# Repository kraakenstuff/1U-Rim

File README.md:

# 1U-RIM
Eurorack 1U rimshot module based on Hexinverter's NeinOhNein Rim (https://static1.squarespace.com/static/54c8f37ae4b015761b133d43/t/550ba520e4b0c15a9e33dd91/1426826530104/?format=1000w)

Status: it worked, but I've redesigned Accent handling. This new PCB is still not tested.

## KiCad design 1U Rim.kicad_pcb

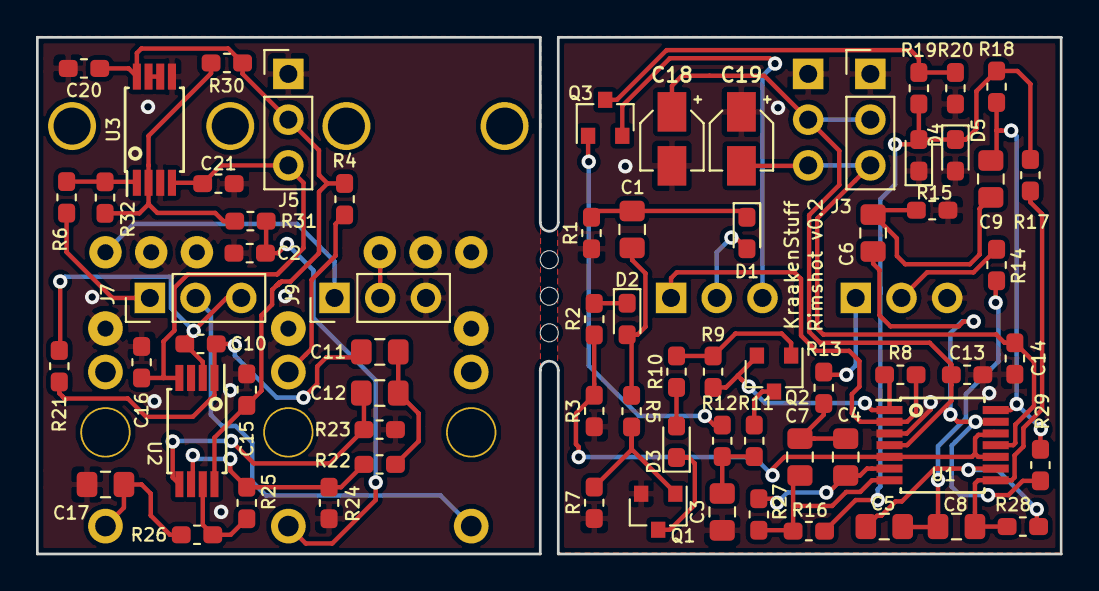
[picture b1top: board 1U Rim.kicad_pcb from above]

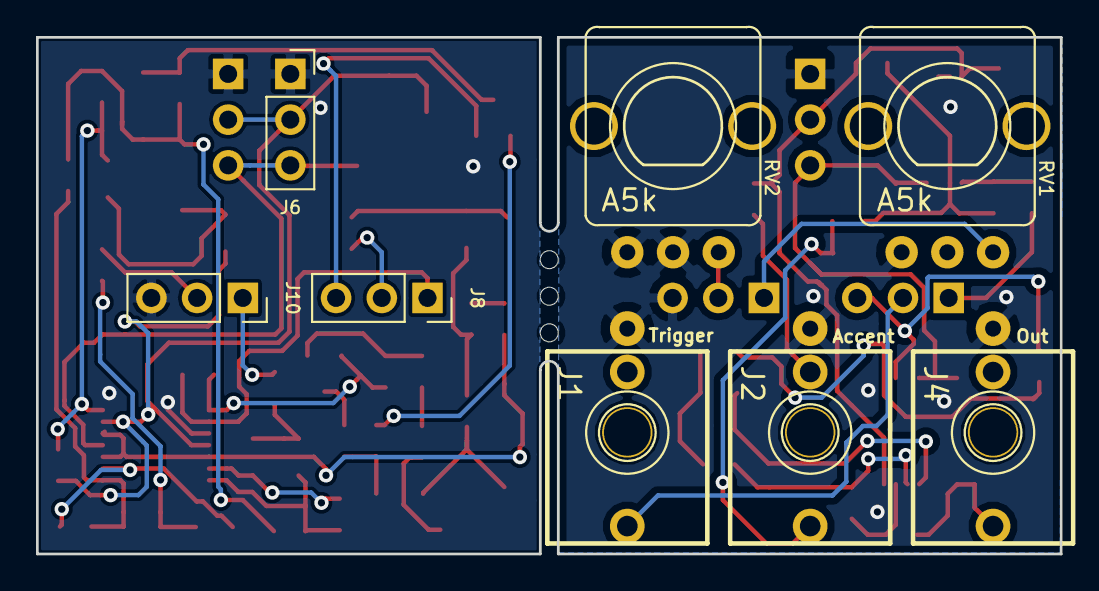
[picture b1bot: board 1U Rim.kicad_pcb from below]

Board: 2 copper layers, 56.9 x 28.7 mm, 76 parts (8 on the bottom side), 42 nets.

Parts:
C1: 18n; C_0805_2012Metric_Pad1.15x1.40mm_HandSolder
C2: 100p; C_0603_1608Metric_Pad1.05x0.95mm_HandSolder
C3: 47n; C_0805_2012Metric_Pad1.15x1.40mm_HandSolder
C4, C7, C11, C12, C17: 10n; C_0805_2012Metric_Pad1.15x1.40mm_HandSolder
C5, C8: 27n; C_0805_2012Metric_Pad1.15x1.40mm_HandSolder
C6, C9: 4.7n; C_0805_2012Metric_Pad1.15x1.40mm_HandSolder
C10: 220p; C_0603_1608Metric_Pad1.05x0.95mm_HandSolder
C13, C14, C15, C16, C20, C21: 100n; C_0603_1608Metric_Pad1.05x0.95mm_HandSolder
C18, C19: 10u; CP_Elec_3x5.3
D1, D2, D3, D4, D5: 1n4148; D_0603_1608Metric_Pad1.05x0.95mm_HandSolder
J1: Trigger; PJ301M-12
J2: Accent; PJ301M-12
J3: PWR; PinHeader_1x03_P2.54mm_Vertical
J4: Out; PJ301M-12
J5: PWR_C; PinHeader_1x03_P2.54mm_Vertical
J6: PWR_M; PinSocket_1x03_P2.54mm_Vertical
J7: JCK_C; PinHeader_1x03_P2.54mm_Vertical
J8: JCK_M; PinSocket_1x03_P2.54mm_Vertical
J9: POT_C; PinHeader_1x03_P2.54mm_Vertical
J10: POT_M; PinSocket_1x03_P2.54mm_Vertical
Q1, Q3: BC849; SOT-23
Q2: BC859; SOT-23
R1, R4, R6, R8, R21, R31, R32: 100k; R_0603_1608Metric_Pad1.05x0.95mm_HandSolder
R2, R3, R5, R22: 22k; R_0603_1608Metric_Pad1.05x0.95mm_HandSolder
R7: 10k; R_0603_1608Metric_Pad1.05x0.95mm_HandSolder
R9, R12: 1M; R_0603_1608Metric_Pad1.05x0.95mm_HandSolder
R10: 47k; R_0603_1608Metric_Pad1.05x0.95mm_HandSolder
R11: 2.7k; R_0603_1608Metric_Pad1.05x0.95mm_HandSolder
R13, R14: 100R; R_0603_1608Metric_Pad1.05x0.95mm_HandSolder
R15: 2.2k; R_0603_1608Metric_Pad1.05x0.95mm_HandSolder
R16, R17, R19: 12k; R_0603_1608Metric_Pad1.05x0.95mm_HandSolder
R18: 3.3k; R_0603_1608Metric_Pad1.05x0.95mm_HandSolder
R20: 680R; R_0603_1608Metric_Pad1.05x0.95mm_HandSolder
R23: 220k; R_0603_1608Metric_Pad1.05x0.95mm_HandSolder
R24, R25: 4.7k; R_0603_1608Metric_Pad1.05x0.95mm_HandSolder
R26: 1k; R_0603_1608Metric_Pad1.05x0.95mm_HandSolder
R27, R29: 470k; R_0603_1608Metric_Pad1.05x0.95mm_HandSolder
R28: 330k; R_0603_1608Metric_Pad1.05x0.95mm_HandSolder
R30: 180k; R_0603_1608Metric_Pad1.05x0.95mm_HandSolder
RV1, RV2: A5k; POT-9MM-ALPHA
U1: TL074; TSSOP-14_4.4x5mm_P0.65mm
U2, U3: TL072; TSSOP-8_4.4x3mm_P0.65mm

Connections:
+12V: C13.2, C15.2, C18.1, C20.2, J3.2, J5.2, J6.2, R4.1, R30.1, U1.4, U2.8, U3.8
-12V: C14.1, C16.1, C19.2, C21.1, J3.3, J5.3, J6.3, U1.11, U2.4, U3.4
Acc: J7.1, J8.1, R6.1, R8.2, U1.2
GND: C2.2, C3.2, C13.1, C14.2, C15.1, C16.2, C17.1, C18.2, C19.1, C20.1, C21.2, D4.1, D5.2, J1.S, J2.S, J3.1, J4.S, J5.1, J6.1, J9.3, J10.3, Q1.2, R1.1, R3.1, R7.1, R15.1, R20.1, R23.1, R24.1, RV1.1, RV1.2, RV2.1, RV2.2, U1.3, U2.3, U3.3, U3.5
unnamed: C1.1, D2.2, R5.1
unnamed: C1.2, D1.1, R1.2
unnamed: C2.1, J2.T, R31.2
unnamed: C3.1, R11.1, R12.1
unnamed: C4.1, C7.2, R13.1
unnamed: C4.2, R27.1, U1.6
unnamed: C5.1, C8.2, R14.1
unnamed: C5.2, R28.1, U1.9
unnamed: C6.1, C9.2, R15.2
unnamed: C6.2, R29.1, U1.13
unnamed: C7.1, R16.2, R27.2, U1.7
unnamed: C8.1, R17.2, R28.2, U1.8
unnamed: C9.1, R18.2, R29.2, U1.14
unnamed: C10.1, C11.2, R21.1, U2.1
unnamed: C11.1, C12.2, R22.2
unnamed: C12.1, R23.2, U2.5
unnamed: C17.2, J4.T, R26.1
unnamed: D2.1, R2.2
unnamed: D3.1, Q1.3
unnamed: D3.2, R10.1
unnamed: D4.2, D5.1, R16.1, R17.1, R18.1, R19.2
unnamed: J2.TN, R4.2
unnamed: Q1.1, R5.2, R7.2
unnamed: Q2.1, R9.1, R10.2
unnamed: Q2.2, R8.1, R9.2, U1.1
unnamed: Q2.3, R11.2
unnamed: Q3.1, R12.2
unnamed: Q3.3, R19.1, R20.2
unnamed: R2.1, R3.2, U1.5, U1.10, U1.12
unnamed: R22.1, R24.2, R25.2, U2.6
unnamed: R25.1, R26.2, U2.7
unnamed: R30.2, R31.1, R32.1, U3.2
unnamed: R6.2, R32.2, U3.1
unnamed: U3.6, U3.7
Out: C10.2, J7.3, J8.3, Q3.2, R21.2, U2.2
Ptc1: J9.1, J10.1, R13.2, RV1.3
Ptc2: J9.2, J10.2, R14.2, RV2.3
Trig: D1.2, J1.T, J7.2, J8.2

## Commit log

2018-11-25 Fixed README mistake
2019-01-09 Finished v0.1
2019-01-10 Fixed an error. Added Gerber files
2019-02-13 PCB refactoring and BOM
2019-02-17 Fixed three missing resistors Fixed pot orientation
2019-02-17 fixed silkscreen
2019-02-17 Exported gerbers and bom for v0.2
2019-02-17 Added a new handling for Accent
2019-02-17 updated gerbers zip
2019-02-24 Added a panel
